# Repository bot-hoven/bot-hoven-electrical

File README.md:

# Bot-Hoven Electrical Repository

The electrical schematics for the bot-hoven hand PCB (left_hand) and controller PCB (mainpcb).

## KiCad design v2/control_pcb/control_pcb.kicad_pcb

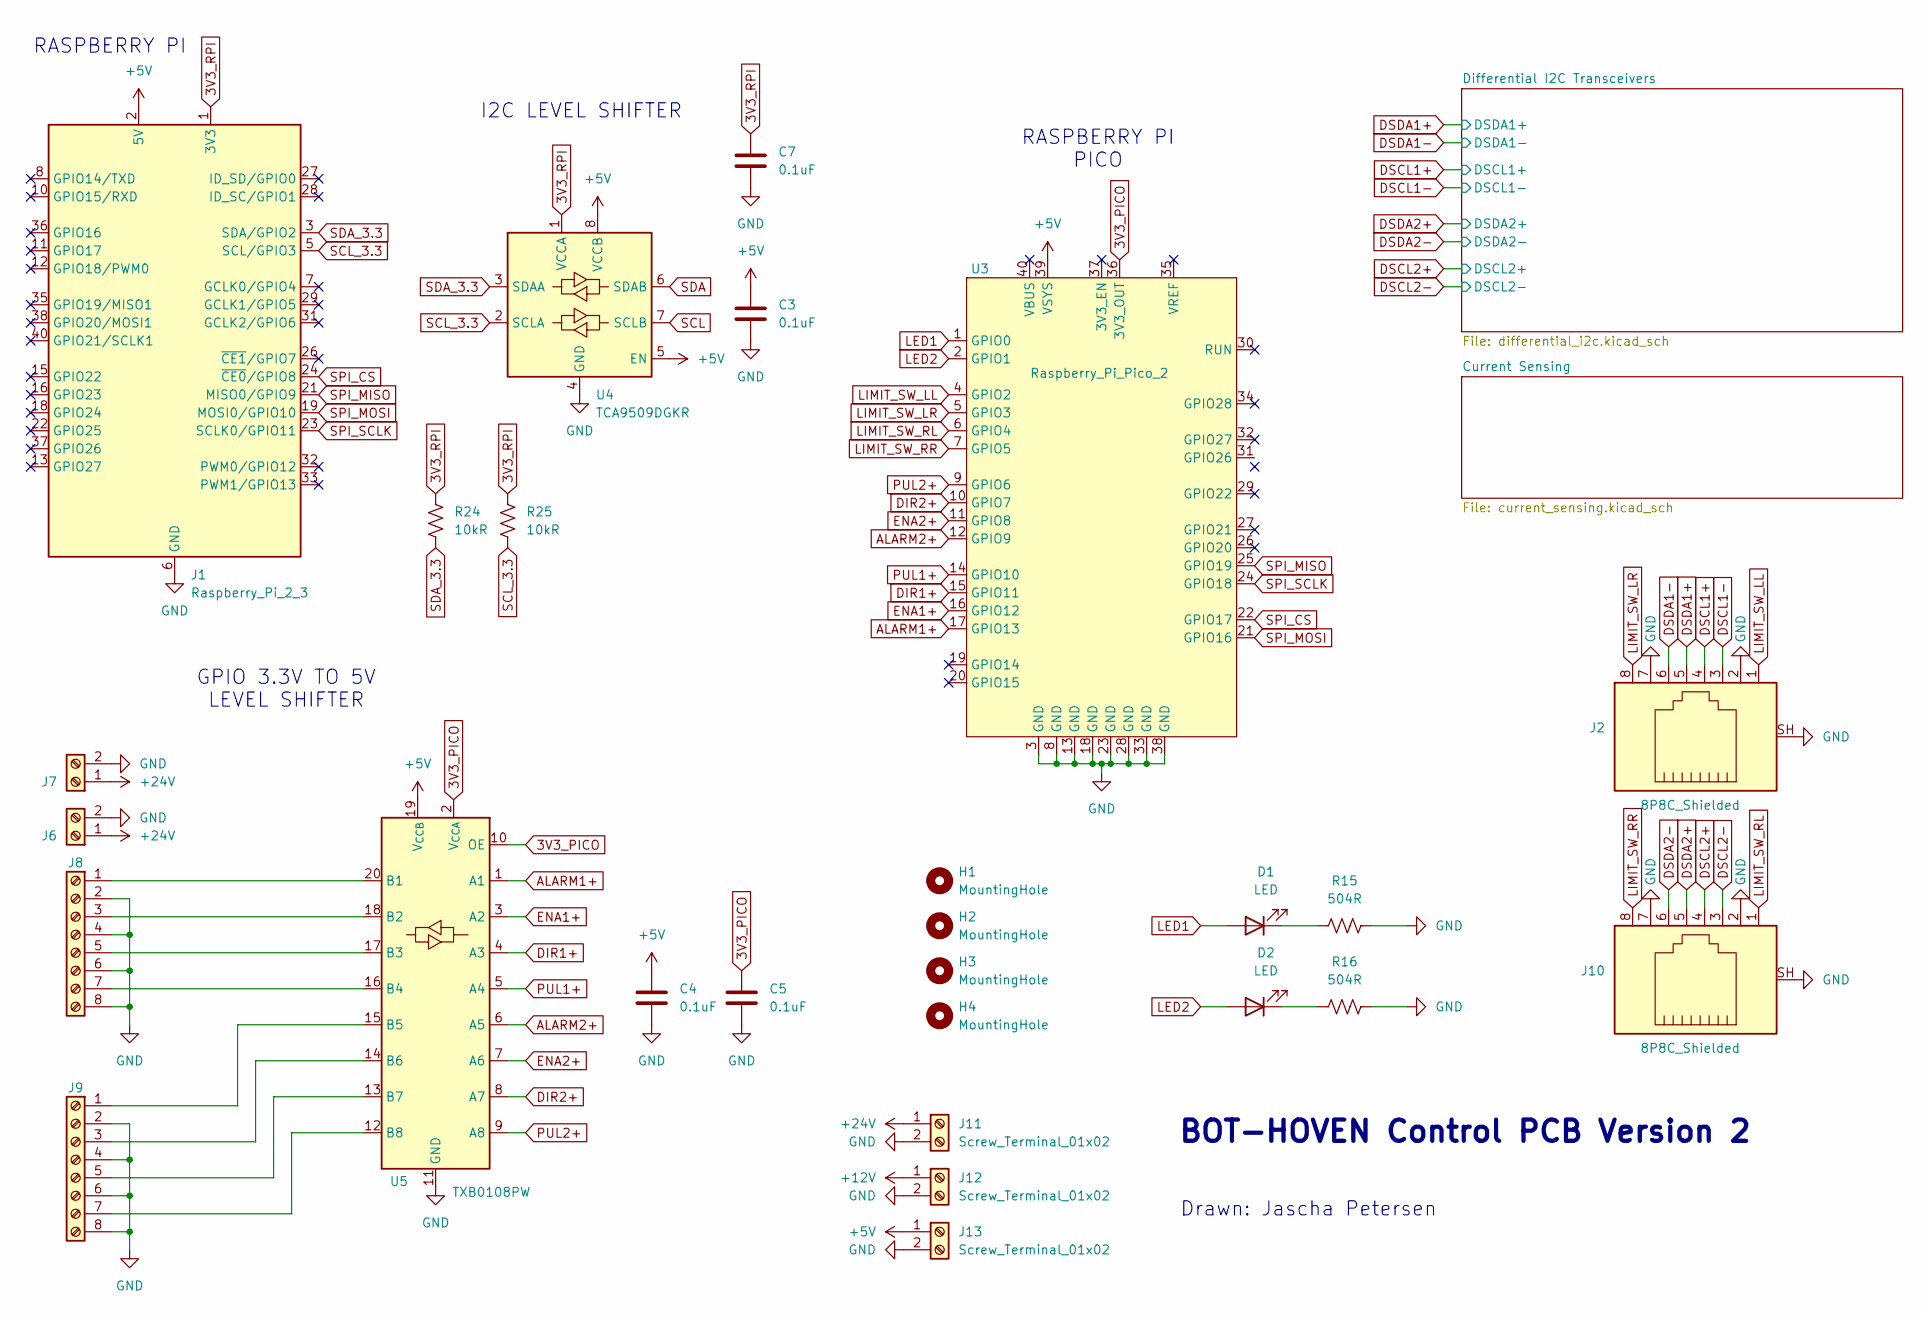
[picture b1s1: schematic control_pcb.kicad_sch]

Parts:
C3, C4, C5, C7: 0.1uF; C_Rect_L4.6mm_W2.0mm_P2.50mm_MKS02_FKP02
D1, D2: LED; LED_D5.0mm_Clear
H1, H2, H3, H4: MountingHole; MountingHole_4.3mm_M4
J1: Raspberry_Pi_2_3; PinHeader_2x20_P2.54mm_Vertical
J2, J10: 8P8C_Shielded; RJ45_Amphenol_54602-x08_Horizontal
J6, J7, J11, J12, J13: Screw_Terminal_01x02; TerminalBlock_Phoenix_PT-1,5-2-5.0-H_1x02_P5.00mm_Horizontal
J8, J9: Screw_Terminal_01x08; TerminalBlock_Phoenix_PT-1,5-8-5.0-H_1x08_P5.00mm_Horizontal
R15, R16: 504R; R_Axial_DIN0207_L6.3mm_D2.5mm_P10.16mm_Horizontal
R24, R25: 10kR; R_Axial_DIN0207_L6.3mm_D2.5mm_P10.16mm_Horizontal
U3: Raspberry_Pi_Pico_2; RaspberryPi_Pico_2_THT
U4: TCA9509DGKR; VSSOP-8_3x3mm_P0.65mm
U5: TXB0108PW; TSSOP-20_4.4x6.5mm_P0.65mm

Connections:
3V3_PICO: C5.1, U3.36 (3V3_OUT), U5.2 (V_{CCA}), U5.10 (OE)
3V3_RPI: C7.1, J1.1 (3V3), J1.17 (3V3), R24.1, R25.1, U4.1 (VCCA)
+5V: C3.1, C4.1, J1.2 (5V), J1.4 (5V), J13.1, U3.39 (VSYS), U4.5 (EN), U4.8 (VCCB), U5.19 (V_{CCB}); also elsewhere on the board
+12V: J12.1; also elsewhere on the board
+24V: J6.1, J7.1, J11.1; also elsewhere on the board
ALARM1+: U3.17 (GPIO13), U5.1 (A1)
ALARM2+: U3.12 (GPIO9), U5.6 (A5)
DIR1+: U3.15 (GPIO11), U5.4 (A3)
DIR2+: U3.10 (GPIO7), U5.8 (A7)
DSCL1+: J2.4; also elsewhere on the board
DSCL1-: J2.3; also elsewhere on the board
DSCL2+: J10.4; also elsewhere on the board
DSCL2-: J10.3; also elsewhere on the board
DSDA1+: J2.5; also elsewhere on the board
DSDA1-: J2.6; also elsewhere on the board
DSDA2+: J10.5; also elsewhere on the board
DSDA2-: J10.6; also elsewhere on the board
ENA1+: U3.16 (GPIO12), U5.3 (A2)
ENA2+: U3.11 (GPIO8), U5.7 (A6)
GND: C3.2, C4.2, C5.2, C7.2, J1.6 (GND), J1.9 (GND), J1.14 (GND), J1.20 (GND), J1.25 (GND), J1.30 (GND), J1.34 (GND), J1.39 (GND), J2.2, J2.7, J2.SH, J6.2, J7.2, J8.2, J8.4, J8.6, J8.8, J9.2, J9.4, J9.6, J9.8, J10.2, J10.7, J10.SH, J11.2, J12.2, J13.2, R15.2, R16.2, U3.3 (GND), U3.8 (GND), U3.13 (GND), U3.18 (GND), U3.23 (GND), U3.28 (GND), U3.33 (GND), U3.38 (GND), U4.4 (GND), U5.11 (GND); also elsewhere on the board
LED1: D1.2 (A), U3.1 (GPIO0)
LED2: D2.2 (A), U3.2 (GPIO1)
LIMIT_SW_LL: J2.1, U3.4 (GPIO2)
LIMIT_SW_LR: J2.8, U3.5 (GPIO3)
LIMIT_SW_RL: J10.1, U3.6 (GPIO4)
LIMIT_SW_RR: J10.8, U3.7 (GPIO5)
unnamed: D1.1 (K), R15.1
unnamed: D2.1 (K), R16.1
unnamed: J8.1, U5.20 (B1)
unnamed: J8.3, U5.18 (B2)
unnamed: J8.5, U5.17 (B3)
unnamed: J8.7, U5.16 (B4)
unnamed: J9.1, U5.15 (B5)
unnamed: J9.3, U5.14 (B6)
unnamed: J9.5, U5.13 (B7)
unnamed: J9.7, U5.12 (B8)
PUL1+: U3.14 (GPIO10), U5.5 (A4)
PUL2+: U3.9 (GPIO6), U5.9 (A8)
SCL: U4.7 (SCLB); also elsewhere on the board
SCL_3.3: J1.5 (SCL/GPIO3), R25.2, U4.2 (SCLA)
SDA: U4.6 (SDAB); also elsewhere on the board
SDA_3.3: J1.3 (SDA/GPIO2), R24.2, U4.3 (SDAA)
SPI_CS: J1.24 (~CE0/GPIO8), U3.22 (GPIO17)
SPI_MISO: J1.21 (MISO0/GPIO9), U3.25 (GPIO19)
SPI_MOSI: J1.19 (MOSI0/GPIO10), U3.21 (GPIO16)
SPI_SCLK: J1.23 (SCLK0/GPIO11), U3.24 (GPIO18)

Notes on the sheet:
BOT-HOVEN Control PCB Version 2
GPIO 3.3V TO 5V LEVEL SHIFTER
I2C LEVEL SHIFTER
Drawn: Jascha Petersen
RASPBERRY PI PICO
RASPBERRY PI

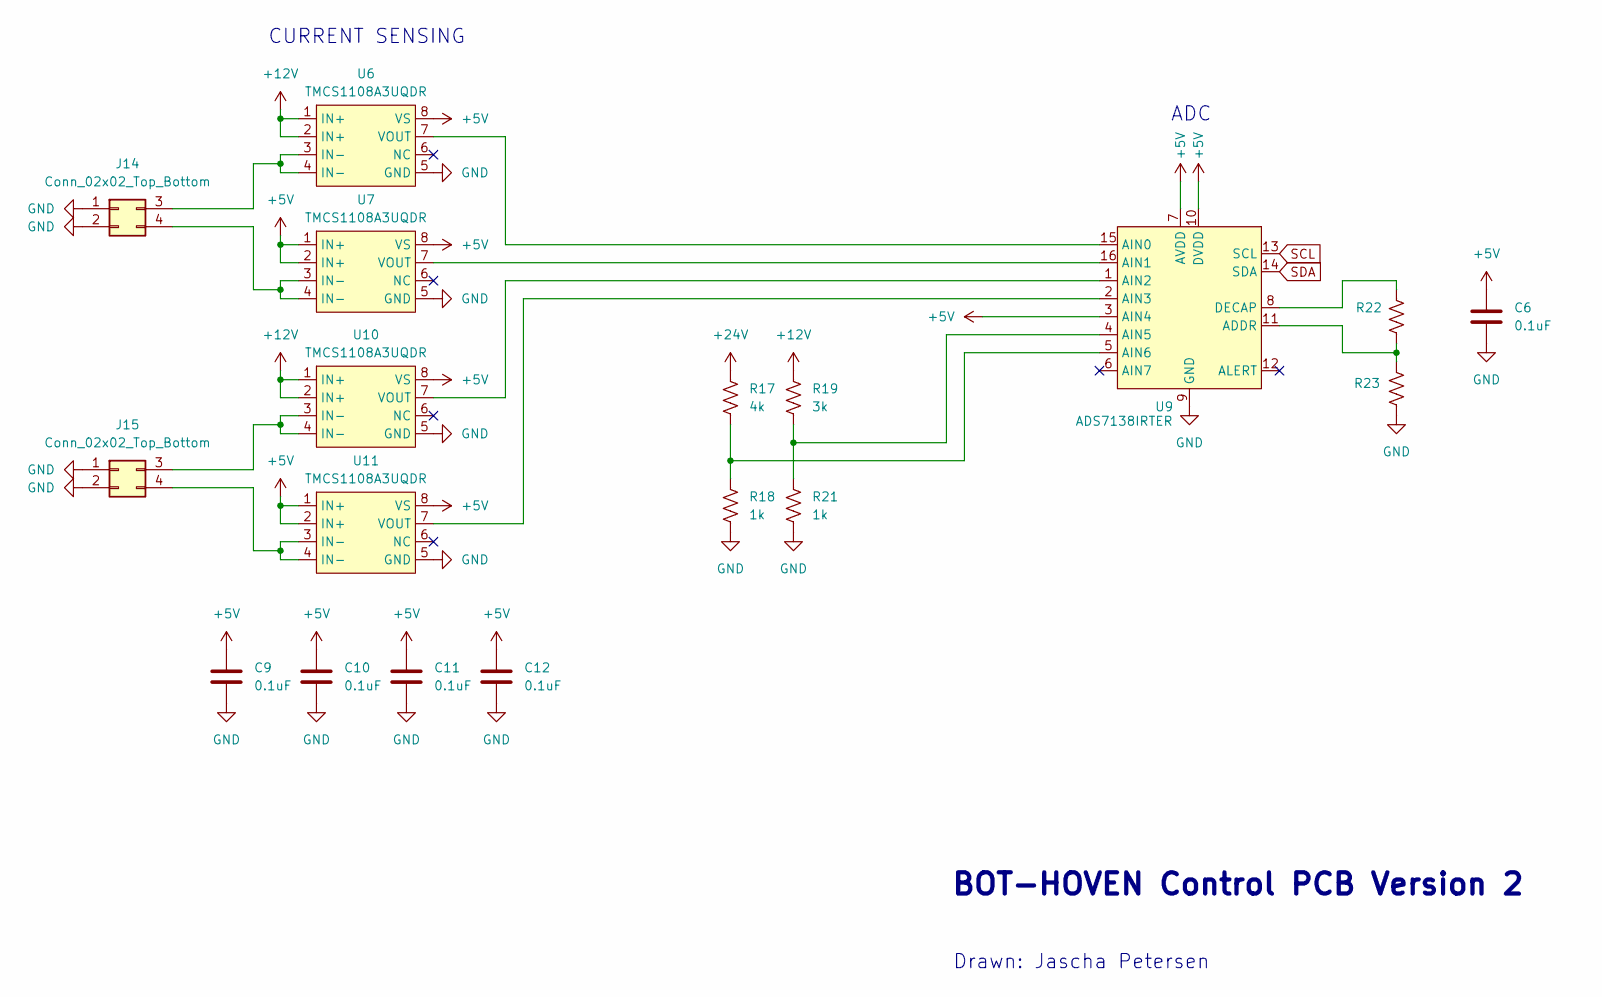
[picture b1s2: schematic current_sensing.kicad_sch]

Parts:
C6, C9, C10, C11, C12: 0.1uF; C_Rect_L4.6mm_W2.0mm_P2.50mm_MKS02_FKP02
J14, J15: Conn_02x02_Top_Bottom; Molex_Mini-Fit_Jr_5569-04A2_2x02_P4.20mm_Horizontal
R17: 4k; R_Axial_DIN0207_L6.3mm_D2.5mm_P10.16mm_Horizontal
R18, R21: 1k; R_Axial_DIN0207_L6.3mm_D2.5mm_P10.16mm_Horizontal
R19: 3k; R_Axial_DIN0207_L6.3mm_D2.5mm_P10.16mm_Horizontal
R22, R23: 0R; R_Axial_DIN0207_L6.3mm_D2.5mm_P10.16mm_Horizontal
U6, U7, U10, U11: TMCS1108A3UQDR; SOIC-8_3.9x4.9mm_P1.27mm
U9: ADS7138IRTER; WQFN-16-1EP_3x3mm_P0.5mm_EP1.68x1.68mm

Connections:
+5V: C6.1, C9.1, C10.1, C11.1, C12.1, U6.8 (VS), U7.1 (IN+), U7.2 (IN+), U7.8 (VS), U9.3 (AIN4), U9.7 (AVDD), U9.10 (DVDD), U10.8 (VS), U11.1 (IN+), U11.2 (IN+), U11.8 (VS); also elsewhere on the board
+12V: R19.1, U6.1 (IN+), U6.2 (IN+), U10.1 (IN+), U10.2 (IN+); also elsewhere on the board
+24V: R17.1; also elsewhere on the board
GND: C6.2, C9.2, C10.2, C11.2, C12.2, J14.1, J14.2, J15.1, J15.2, R18.2, R21.2, R23.2, U6.5 (GND), U7.5 (GND), U9.9 (GND), U10.5 (GND), U11.5 (GND); also elsewhere on the board
unnamed: J14.3, U6.3 (IN-), U6.4 (IN-)
unnamed: J14.4, U7.3 (IN-), U7.4 (IN-)
unnamed: J15.3, U10.3 (IN-), U10.4 (IN-)
unnamed: J15.4, U11.3 (IN-), U11.4 (IN-)
unnamed: U6.7 (VOUT), U9.15 (AIN0)
unnamed: U7.7 (VOUT), U9.16 (AIN1)
unnamed: R22.2, R23.1, U9.11 (ADDR)
unnamed: R19.2, R21.1, U9.4 (AIN5)
unnamed: R17.2, R18.1, U9.5 (AIN6)
unnamed: R22.1, U9.8 (DECAP)
unnamed: U9.1 (AIN2), U10.7 (VOUT)
unnamed: U9.2 (AIN3), U11.7 (VOUT)
SCL: U9.13 (SCL); also elsewhere on the board
SDA: U9.14 (SDA); also elsewhere on the board

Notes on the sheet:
ADC
CURRENT SENSING
Drawn: Jascha Petersen
BOT-HOVEN Control PCB Version 2

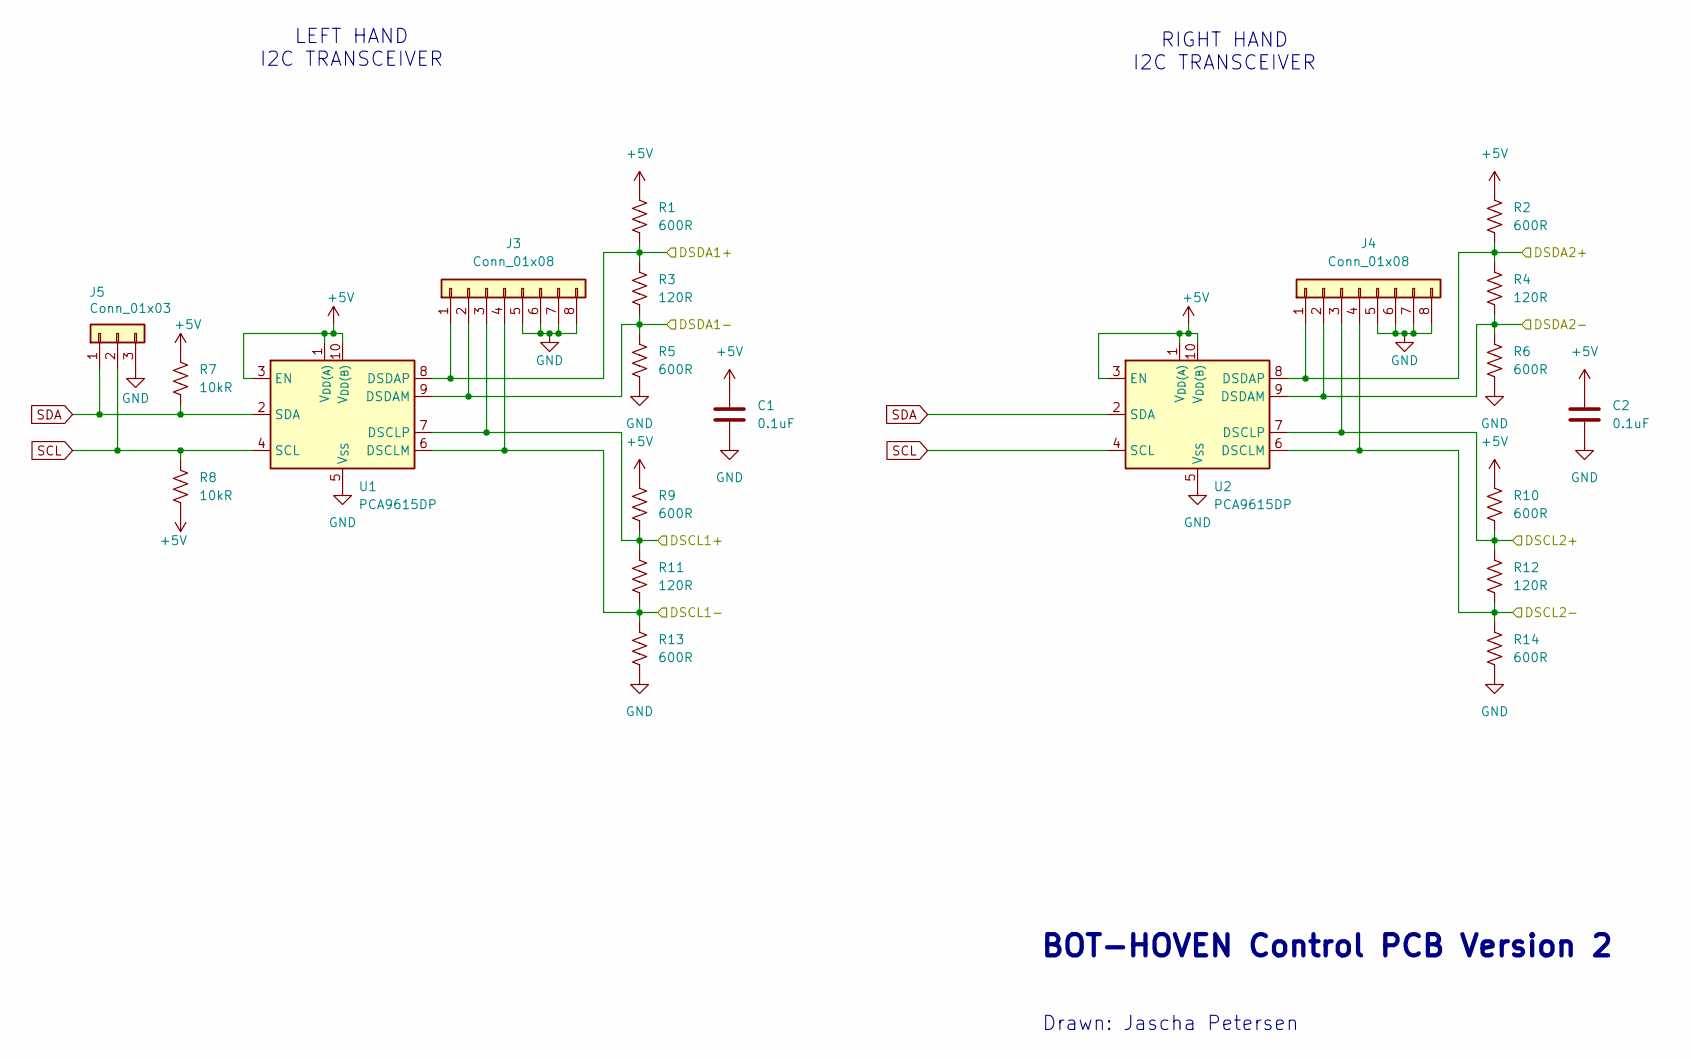
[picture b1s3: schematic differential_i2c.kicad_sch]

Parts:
C1, C2: 0.1uF; C_Rect_L4.6mm_W2.0mm_P2.50mm_MKS02_FKP02
J3, J4: Conn_01x08; PinHeader_1x08_P2.54mm_Vertical
J5: Conn_01x03; PinHeader_1x03_P2.54mm_Vertical
R1, R2, R5, R6, R9, R10, R13, R14: 600R; R_Axial_DIN0207_L6.3mm_D2.5mm_P10.16mm_Horizontal
R3, R4, R11, R12: 120R; R_Axial_DIN0207_L6.3mm_D2.5mm_P10.16mm_Horizontal
R7, R8: 10kR; R_Axial_DIN0207_L6.3mm_D2.5mm_P10.16mm_Horizontal
U1, U2: PCA9615DP; TSSOP-10_3x3mm_P0.5mm

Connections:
+5V: C1.1, C2.1, R1.1, R2.1, R7.1, R8.2, R9.1, R10.1, U1.1 (V_{DD(A)}), U1.3 (EN), U1.10 (V_{DD(B)}), U2.1 (V_{DD(A)}), U2.3 (EN), U2.10 (V_{DD(B)}); also elsewhere on the board
DSCL1+: J3.3, R9.2, R11.1, U1.7 (DSCLP); also elsewhere on the board
DSCL1-: J3.4, R11.2, R13.1, U1.6 (DSCLM); also elsewhere on the board
DSCL2+: J4.3, R10.2, R12.1, U2.7 (DSCLP); also elsewhere on the board
DSCL2-: J4.4, R12.2, R14.1, U2.6 (DSCLM); also elsewhere on the board
DSDA1+: J3.1, R1.2, R3.1, U1.8 (DSDAP); also elsewhere on the board
DSDA1-: J3.2, R3.2, R5.1, U1.9 (DSDAM); also elsewhere on the board
DSDA2+: J4.1, R2.2, R4.1, U2.8 (DSDAP); also elsewhere on the board
DSDA2-: J4.2, R4.2, R6.1, U2.9 (DSDAM); also elsewhere on the board
GND: C1.2, C2.2, J3.5, J3.6, J3.7, J3.8, J4.5, J4.6, J4.7, J4.8, J5.3, R5.2, R6.2, R13.2, R14.2, U1.5 (V_{SS}), U2.5 (V_{SS}); also elsewhere on the board
SCL: J5.2, R8.1, U1.4 (SCL), U2.4 (SCL); also elsewhere on the board
SDA: J5.1, R7.2, U1.2 (SDA), U2.2 (SDA); also elsewhere on the board

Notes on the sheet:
BOT-HOVEN Control PCB Version 2
RIGHT HAND I2C TRANSCEIVER
LEFT HAND I2C TRANSCEIVER
Drawn: Jascha Petersen

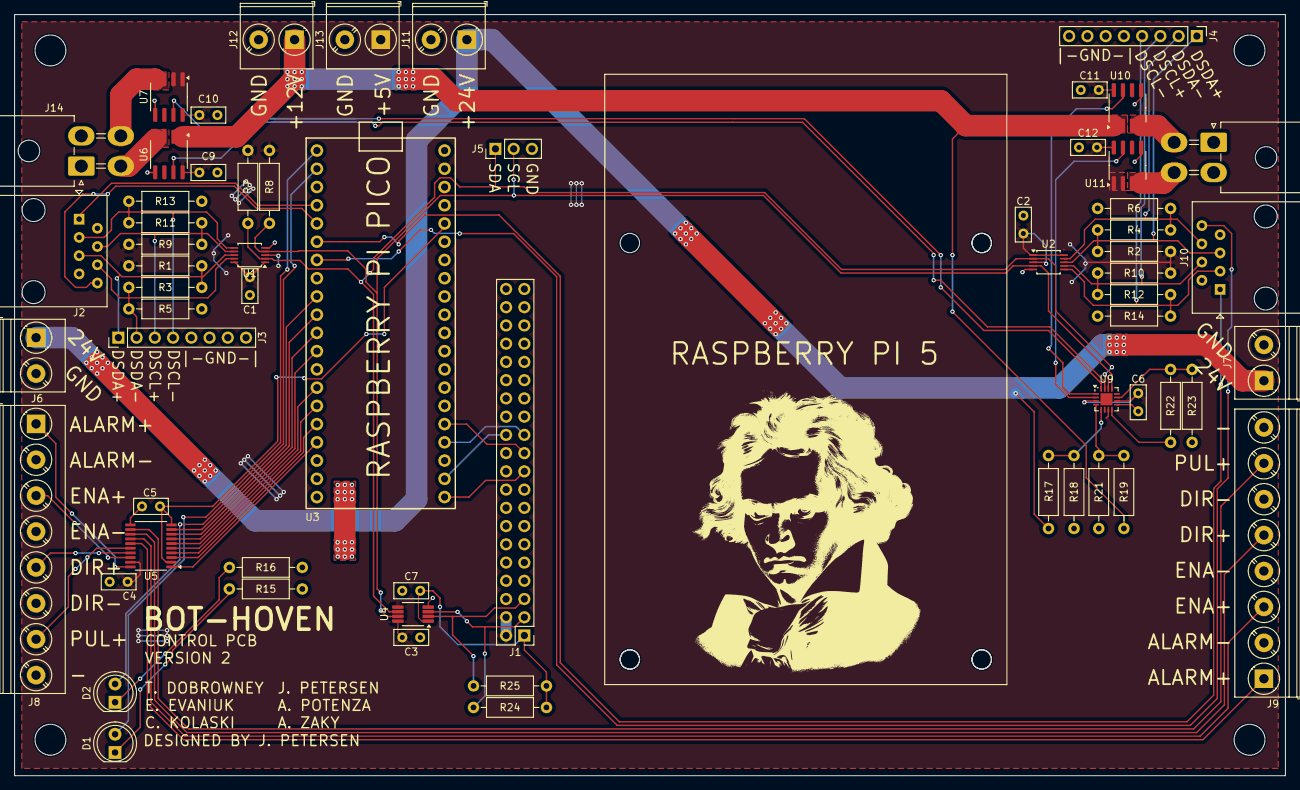
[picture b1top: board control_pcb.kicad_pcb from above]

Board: 2 copper layers, 177.0 x 106.0 mm, 66 parts (0 on the bottom side), 58 nets.

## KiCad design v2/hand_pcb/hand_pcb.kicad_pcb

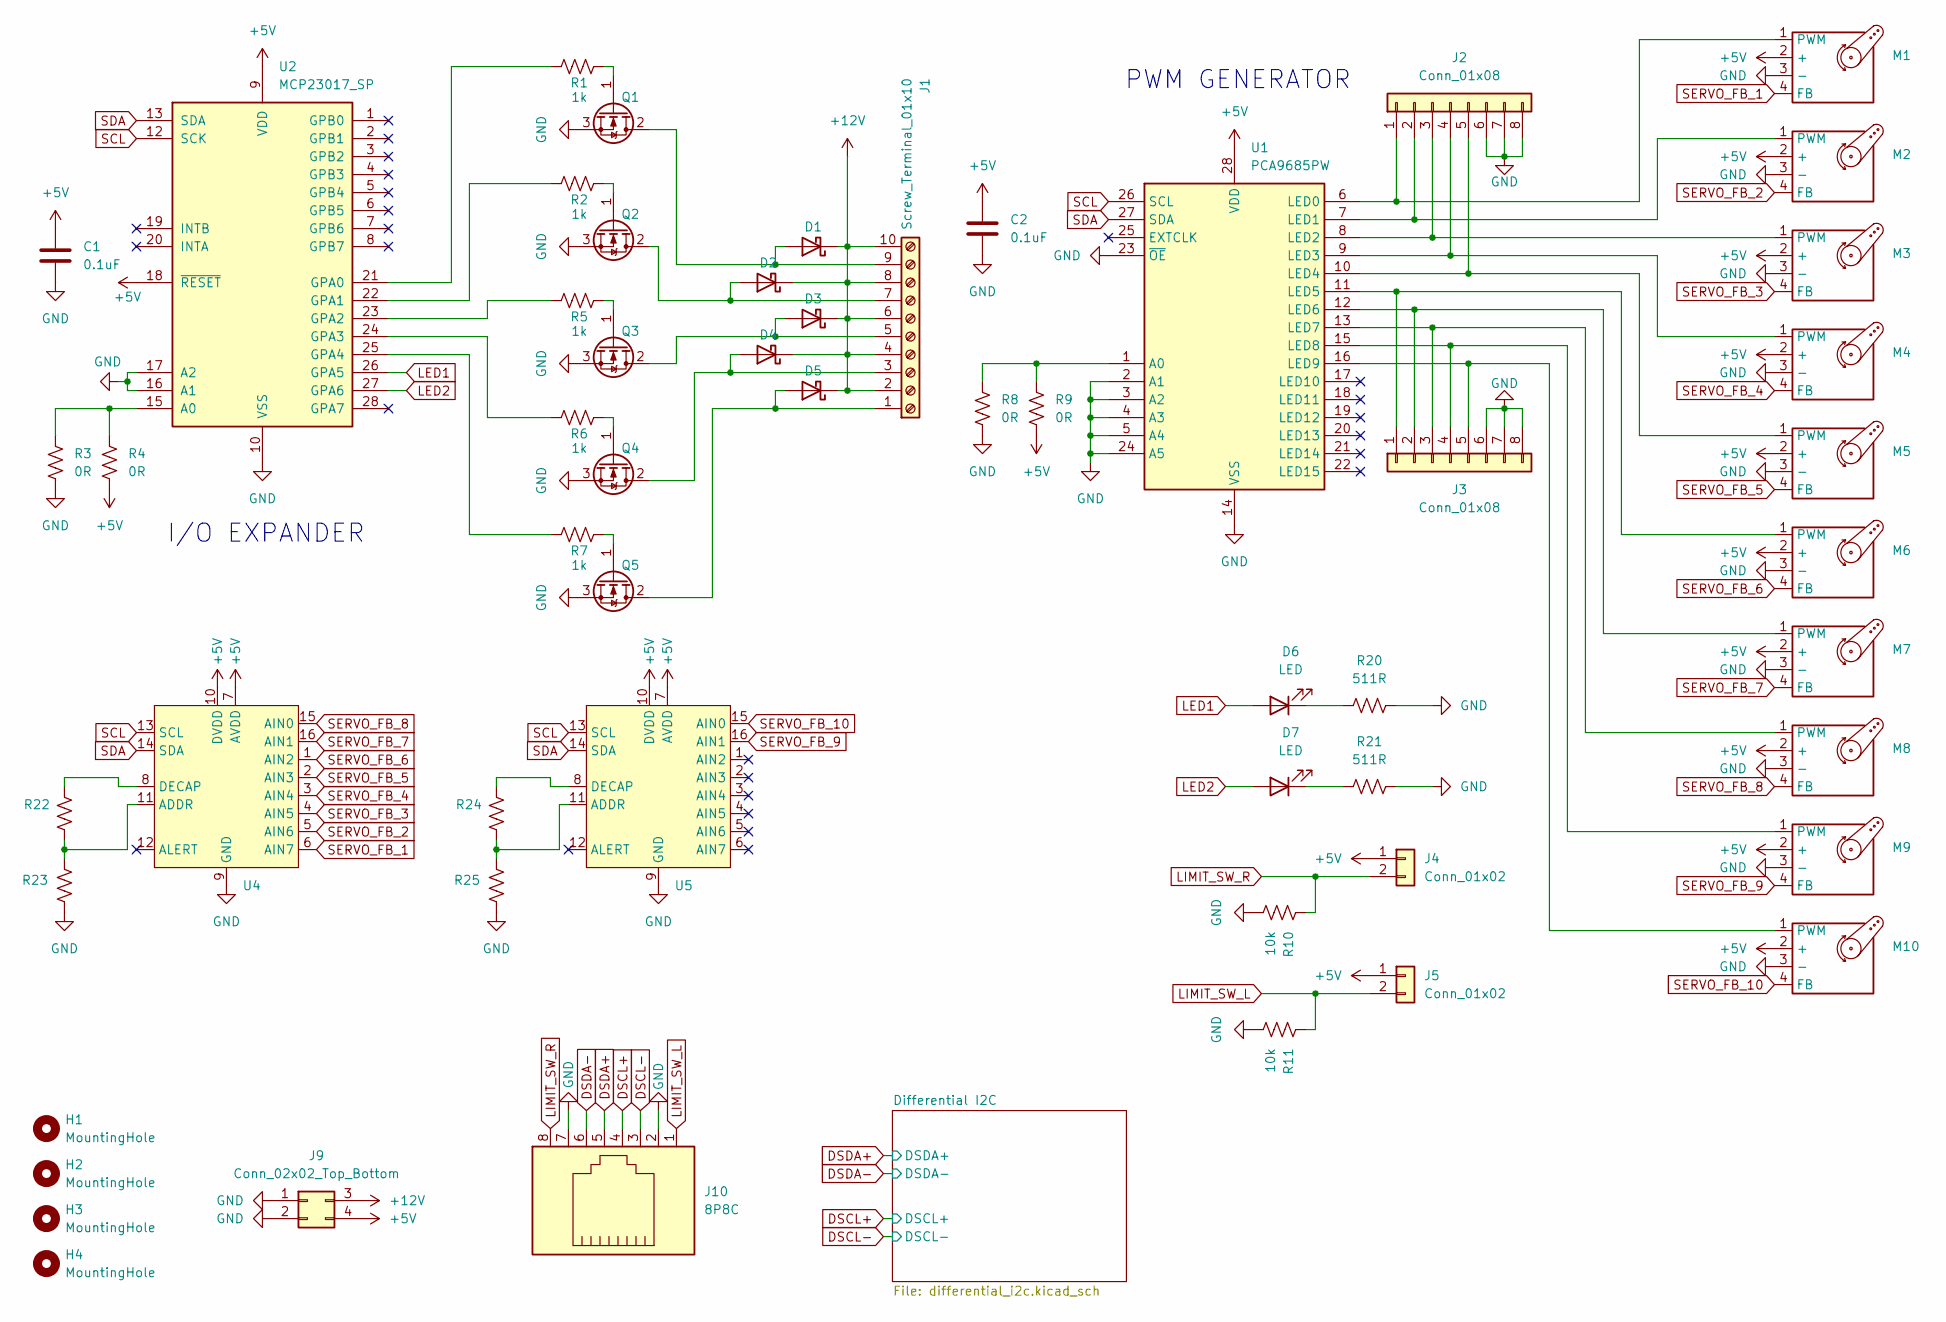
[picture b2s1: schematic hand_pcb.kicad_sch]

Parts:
C1, C2: 0.1uF; C_Disc_D3.4mm_W2.1mm_P2.50mm
D1, D2, D3, D4, D5: SB5100-T; D_DO-201AD_P12.70mm_Horizontal
D6, D7: LED; LED_D5.0mm_Clear
H1, H2, H3, H4: MountingHole; MountingHole_3.2mm_M3
J1: Screw_Terminal_01x10; TerminalBlock_Phoenix_PT-1,5-10-5.0-H_1x10_P5.00mm_Horizont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
J2, J3: Conn_01x08; PinHeader_1x08_P2.54mm_Vertical
J4, J5: Conn_01x02; JST_XH_S2B-XH-A_1x02_P2.50mm_Horizontal
J9: Conn_02x02_Top_Bottom; Molex_Mini-Fit_Jr_5569-04A2_2x02_P4.20mm_Horizontal
J10: 8P8C; RJ45_Amphenol_54602-x08_Horizontal
M1, M2, M3, M4, M5, M6, M7, M8, M9, M10: Motor_Servo_FB; PinHeader_1x04_P2.54mm_Vertical
Q1, Q2, Q3, Q4, Q5: Q_NMOS_GDS; TO-220-3_Vertical
R1, R2, R5, R6, R7: 1k; R_Axial_DIN0207_L6.3mm_D2.5mm_P10.16mm_Horizontal
R3, R4, R8, R9, R22, R23, R24, R25: 0R; R_Axial_DIN0207_L6.3mm_D2.5mm_P10.16mm_Horizontal
R10, R11: 10k; R_Axial_DIN0207_L6.3mm_D2.5mm_P10.16mm_Horizontal
R20, R21: 511R; R_Axial_DIN0207_L6.3mm_D2.5mm_P10.16mm_Horizontal
U1: PCA9685PW; TSSOP-28_4.4x9.7mm_P0.65mm
U2: MCP23017_SP; DIP-28_W7.62mm
U4, U5: WQFN-16-1EP_3x3mm_P0.5mm_EP1.68x1.68mm

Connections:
+5V: C1.1, C2.1, J4.1, J5.1, J9.4, M1.2 (+), M2.2 (+), M3.2 (+), M4.2 (+), M5.2 (+), M6.2 (+), M7.2 (+), M8.2 (+), M9.2 (+), M10.2 (+), R4.2, R9.2, U1.28 (VDD), U2.9 (VDD), U2.18 (~RESET), U4.7 (AVDD), U4.10 (DVDD), U5.7 (AVDD), U5.10 (DVDD); also elsewhere on the board
+12V: D1.1 (K), D2.1 (K), D3.1 (K), D4.1 (K), D5.1 (K), J1.2, J1.4, J1.6, J1.8, J1.10, J9.3
DSCL+: J10.4; also elsewhere on the board
DSCL-: J10.3; also elsewhere on the board
DSDA+: J10.5; also elsewhere on the board
DSDA-: J10.6; also elsewhere on the board
GND: C1.2, C2.2, J2.6, J2.7, J2.8, J3.6, J3.7, J3.8, J9.1, J9.2, J10.2, J10.7, M1.3 (-), M2.3 (-), M3.3 (-), M4.3 (-), M5.3 (-), M6.3 (-), M7.3 (-), M8.3 (-), M9.3 (-), M10.3 (-), Q1.3 (S), Q2.3 (S), Q3.3 (S), Q4.3 (S), Q5.3 (S), R3.2, R8.2, R10.1, R11.1, R20.2, R21.2, R23.2, R25.2, U1.2 (A1), U1.3 (A2), U1.4 (A3), U1.5 (A4), U1.14 (VSS), U1.23 (~OE), U1.24 (A5), U2.10 (VSS), U2.16 (A1), U2.17 (A2), U4.9 (GND), U5.9 (GND); also elsewhere on the board
LED1: D6.2 (A), U2.26 (GPA5)
LED2: D7.2 (A), U2.27 (GPA6)
LIMIT_SW_L: J5.2, J10.1, R11.2
LIMIT_SW_R: J4.2, J10.8, R10.2
unnamed: D1.2 (A), J1.9, Q1.2 (D)
unnamed: D2.2 (A), J1.7, Q2.2 (D)
unnamed: D3.2 (A), J1.5, Q3.2 (D)
unnamed: D4.2 (A), J1.3, Q4.2 (D)
unnamed: D5.2 (A), J1.1, Q5.2 (D)
unnamed: D6.1 (K), R20.1
unnamed: D7.1 (K), R21.1
unnamed: J2.1, M1.1 (PWM), U1.6 (LED0)
unnamed: J2.2, M2.1 (PWM), U1.7 (LED1)
unnamed: J2.3, M3.1 (PWM), U1.8 (LED2)
unnamed: J2.4, M4.1 (PWM), U1.9 (LED3)
unnamed: J2.5, M5.1 (PWM), U1.10 (LED4)
unnamed: J3.1, M6.1 (PWM), U1.11 (LED5)
unnamed: J3.2, M7.1 (PWM), U1.12 (LED6)
unnamed: J3.3, M8.1 (PWM), U1.13 (LED7)
unnamed: J3.4, M9.1 (PWM), U1.15 (LED8)
unnamed: J3.5, M10.1 (PWM), U1.16 (LED9)
unnamed: Q1.1 (G), R1.2
unnamed: Q2.1 (G), R2.2
unnamed: Q3.1 (G), R5.2
unnamed: Q4.1 (G), R6.2
unnamed: Q5.1 (G), R7.2
unnamed: R8.1, R9.1, U1.1 (A0)
unnamed: R3.1, R4.1, U2.15 (A0)
unnamed: R1.1, U2.21 (GPA0)
unnamed: R2.1, U2.22 (GPA1)
unnamed: R5.1, U2.23 (GPA2)
unnamed: R6.1, U2.24 (GPA3)
unnamed: R7.1, U2.25 (GPA4)
unnamed: R22.2, R23.1, U4.11 (ADDR)
unnamed: R22.1, U4.8 (DECAP)
unnamed: R24.2, R25.1, U5.11 (ADDR)
unnamed: R24.1, U5.8 (DECAP)
SCL: U1.26 (SCL), U2.12 (SCK), U4.13 (SCL), U5.13 (SCL); also elsewhere on the board
SDA: U1.27 (SDA), U2.13 (SDA), U4.14 (SDA), U5.14 (SDA); also elsewhere on the board
SERVO_FB_1: M1.4 (FB), U4.6 (AIN7)
SERVO_FB_2: M2.4 (FB), U4.5 (AIN6)
SERVO_FB_3: M3.4 (FB), U4.4 (AIN5)
SERVO_FB_4: M4.4 (FB), U4.3 (AIN4)
SERVO_FB_5: M5.4 (FB), U4.2 (AIN3)
SERVO_FB_6: M6.4 (FB), U4.1 (AIN2)
SERVO_FB_7: M7.4 (FB), U4.16 (AIN1)
SERVO_FB_8: M8.4 (FB), U4.15 (AIN0)
SERVO_FB_9: M9.4 (FB), U5.16 (AIN1)
SERVO_FB_10: M10.4 (FB), U5.15 (AIN0)

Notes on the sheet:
I/O EXPANDER
PWM GENERATOR

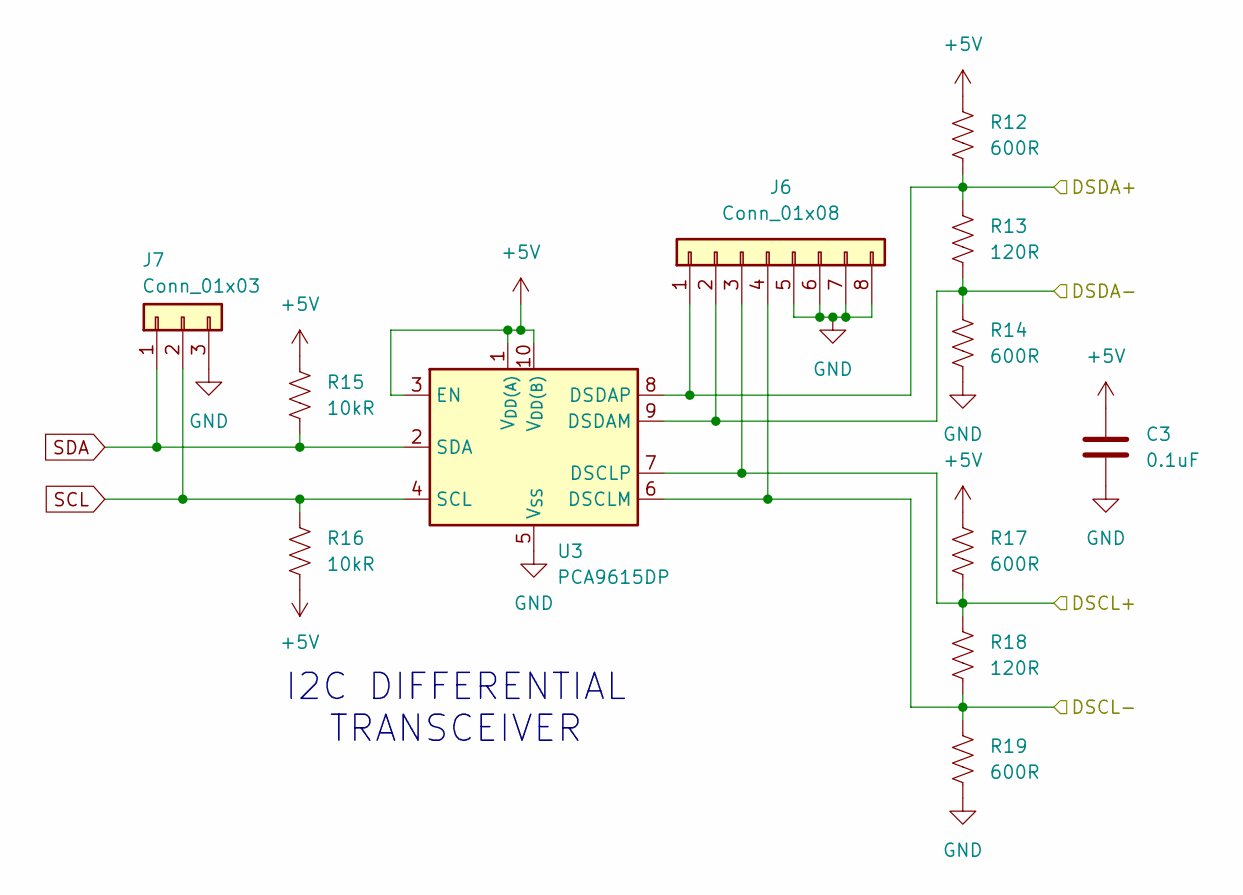
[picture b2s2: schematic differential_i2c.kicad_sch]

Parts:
C3: 0.1uF; C_Disc_D3.4mm_W2.1mm_P2.50mm
J6: Conn_01x08; PinHeader_1x08_P2.54mm_Vertical
J7: Conn_01x03; PinHeader_1x03_P2.54mm_Vertical
R12, R14, R17, R19: 600R; R_Axial_DIN0207_L6.3mm_D2.5mm_P10.16mm_Horizontal
R13, R18: 120R; R_Axial_DIN0207_L6.3mm_D2.5mm_P10.16mm_Horizontal
R15, R16: 10kR; R_Axial_DIN0207_L6.3mm_D2.5mm_P10.16mm_Horizontal
U3: PCA9615DP; TSSOP-10_3x3mm_P0.5mm

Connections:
+5V: C3.1, R12.1, R15.1, R16.2, R17.1, U3.1 (V_{DD(A)}), U3.3 (EN), U3.10 (V_{DD(B)}); also elsewhere on the board
DSCL+: J6.3, R17.2, R18.1, U3.7 (DSCLP); also elsewhere on the board
DSCL-: J6.4, R18.2, R19.1, U3.6 (DSCLM); also elsewhere on the board
DSDA+: J6.1, R12.2, R13.1, U3.8 (DSDAP); also elsewhere on the board
DSDA-: J6.2, R13.2, R14.1, U3.9 (DSDAM); also elsewhere on the board
GND: C3.2, J6.5, J6.6, J6.7, J6.8, J7.3, R14.2, R19.2, U3.5 (V_{SS}); also elsewhere on the board
SCL: J7.2, R16.1, U3.4 (SCL); also elsewhere on the board
SDA: J7.1, R15.2, U3.2 (SDA); also elsewhere on the board

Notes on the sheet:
I2C DIFFERENTIAL TRANSCEIVER

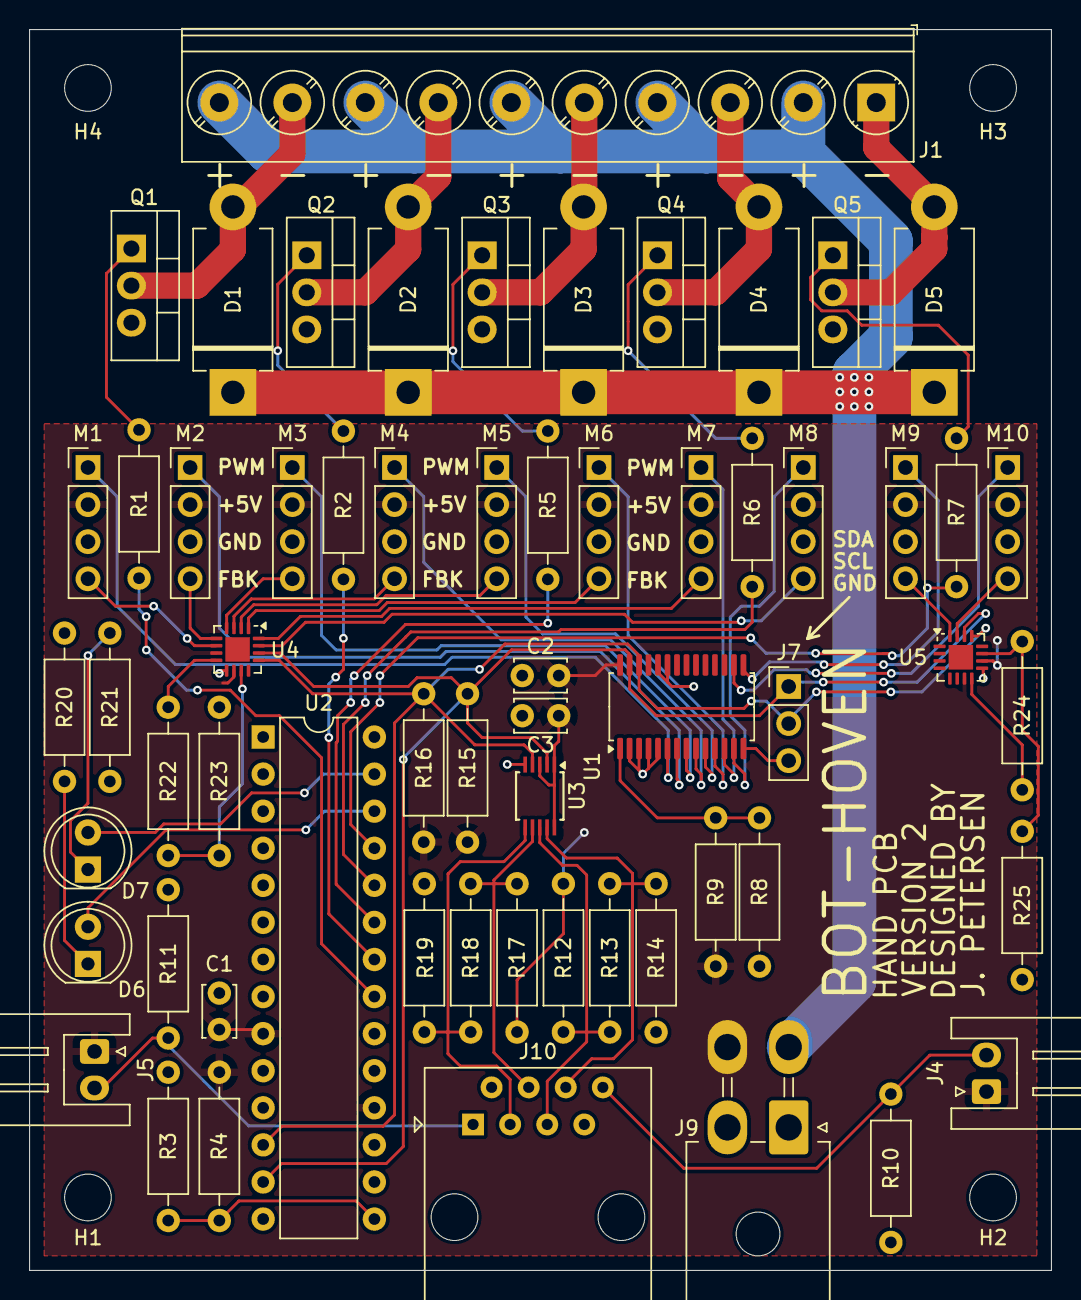
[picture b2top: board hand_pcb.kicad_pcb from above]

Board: 2 copper layers, 70.0 x 85.0 mm, 65 parts (0 on the bottom side), 56 nets.
